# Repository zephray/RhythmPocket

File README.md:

# RhythmPocket
Pocket audio player inside GameBoy case

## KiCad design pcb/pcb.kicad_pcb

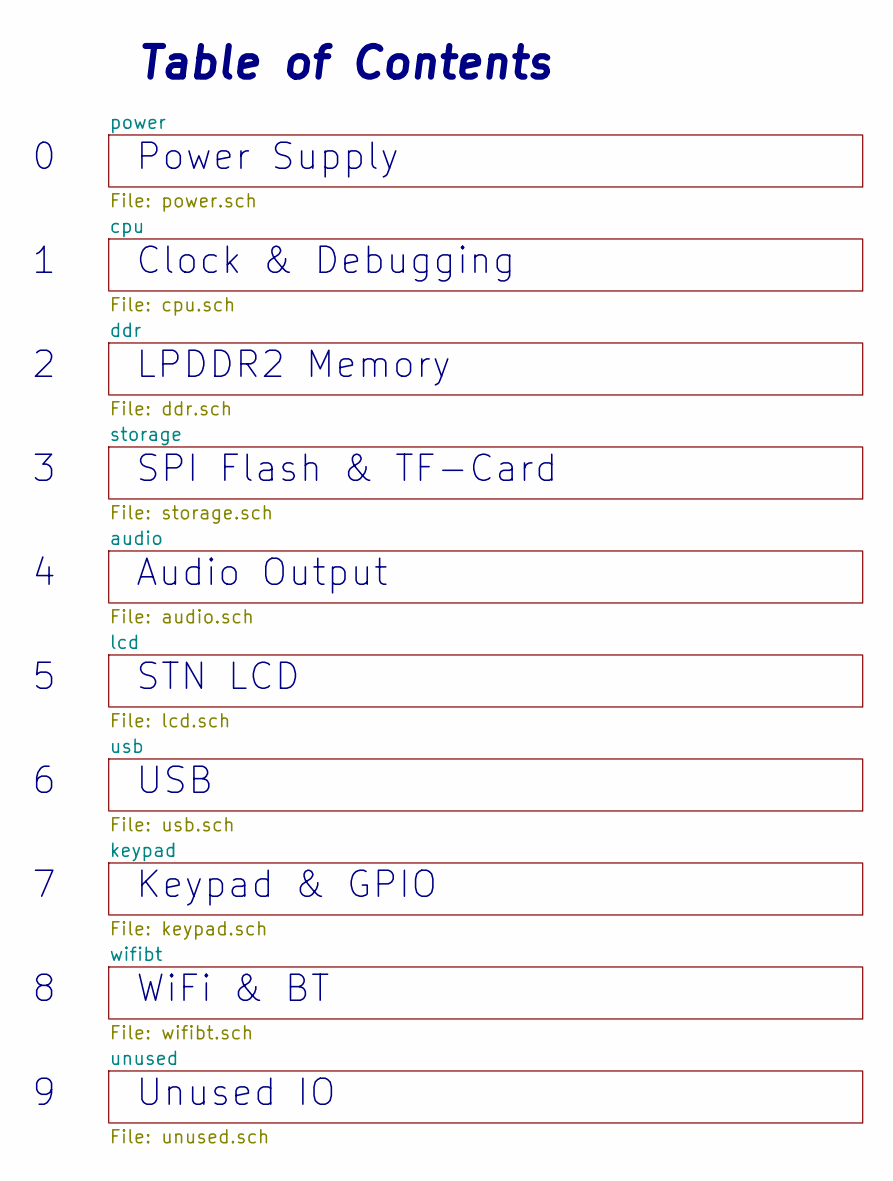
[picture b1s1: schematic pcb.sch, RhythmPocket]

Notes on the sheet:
Clock & Debugging
LPDDR2 Memory
STN LCD
SPI Flash & TF-Card
Table of Contents
Power Supply
Audio Output
Keypad & GPIO
Unused IO
USB
WiFi & BT

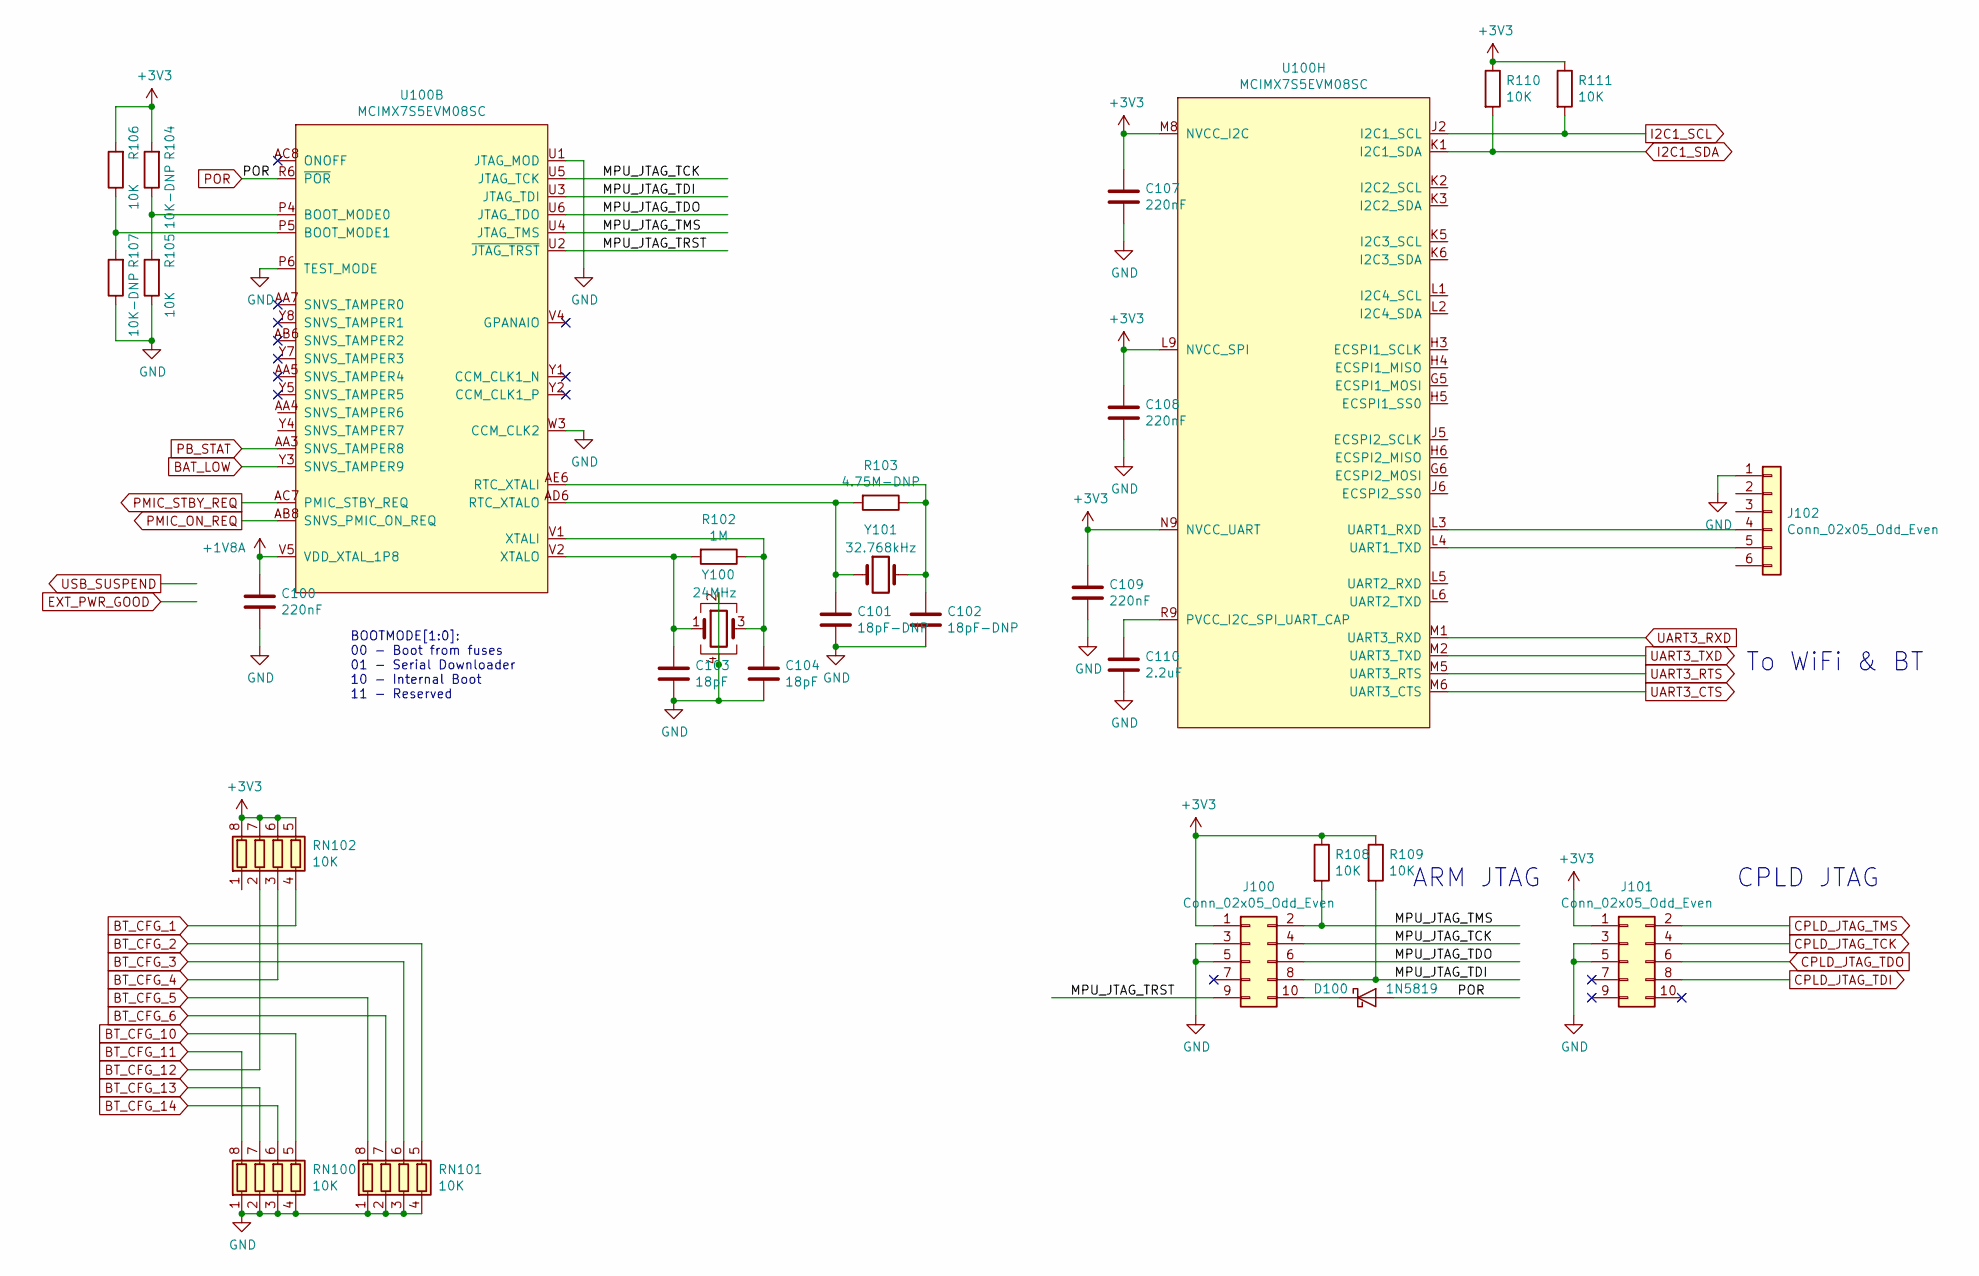
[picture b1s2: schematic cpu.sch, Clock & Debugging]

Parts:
C100, C107, C108, C109: 220nF; C_0402_1005Metric
C101, C102: 18pF-DNP; C_0402_1005Metric
C103, C104: 18pF; C_0402_1005Metric
C110: 2.2uF; C_0402_1005Metric
D100: 1N5819; D_SOD-123
J100, J101, J102: Conn_02x05_Odd_Even; PinHeader_2x05_P1.27mm_Vertical_SMD
R102: 1M; R_0603_1608Metric
R103: 4.75M-DNP; R_0603_1608Metric
R104, R107: 10K-DNP; R_0603_1608Metric
R105, R106, R108, R109, R110, R111: 10K; R_0603_1608Metric
RN100, RN101, RN102: 10K; R_Array_Convex_4x0402
U100: MCIMX7S5EVM08SC; BGA-541_25x25_19.0x19.0mm
Y100: 24MHz; Oscillator_SMD_Abracon_ASE-4Pin_3.2x2.5mm
Y101: 32.768kHz; Crystal_SMD_TXC_9HT11-2Pin_2.0x1.2mm_HandSoldering

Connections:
+1V8A: C100.1, U100.V5 (VDD_XTAL_1P8)
+3V3: C107.1, C108.1, C109.1, J100.1, J101.1, R104.2, R106.2, R108.1, R109.1, R110.1, R111.1, RN102.5 (R4.2), RN102.6 (R3.2), RN102.7 (R2.2), RN102.8 (R1.2), U100.L9 (NVCC_SPI), U100.M8 (NVCC_I2C), U100.N9 (NVCC_UART); also elsewhere on the board
/cpu/MPU_JTAG_TCK: J100.4, U100.U5 (JTAG_TCK)
/cpu/MPU_JTAG_TDI: J100.8, R109.2, U100.U3 (JTAG_TDI)
/cpu/MPU_JTAG_TDO: J100.6, U100.U6 (JTAG_TDO)
/cpu/MPU_JTAG_TMS: J100.2, R108.2, U100.U4 (JTAG_TMS)
/cpu/MPU_JTAG_TRST: J100.9, U100.U2 (~JTAG_TRST)
BAT_LOW: U100.Y3 (SNVS_TAMPER9); also elsewhere on the board
BT_CFG_1: RN102.4 (R4.1); also elsewhere on the board
BT_CFG_2: RN101.5 (R4.2); also elsewhere on the board
BT_CFG_3: RN101.6 (R3.2); also elsewhere on the board
BT_CFG_4: RN102.3 (R3.1); also elsewhere on the board
BT_CFG_5: RN101.8 (R1.2); also elsewhere on the board
BT_CFG_6: RN101.7 (R2.2); also elsewhere on the board
BT_CFG_10: RN100.5 (R4.2); also elsewhere on the board
BT_CFG_11: RN100.8 (R1.2); also elsewhere on the board
BT_CFG_12: RN102.2 (R2.1); also elsewhere on the board
BT_CFG_13: RN100.7 (R2.2); also elsewhere on the board
BT_CFG_14: RN100.6 (R3.2); also elsewhere on the board
CPLD_JTAG_TCK: J101.4; also elsewhere on the board
CPLD_JTAG_TDI: J101.8; also elsewhere on the board
CPLD_JTAG_TDO: J101.6; also elsewhere on the board
CPLD_JTAG_TMS: J101.2; also elsewhere on the board
GND: C100.2, C101.2, C102.2, C103.2, C104.2, C107.2, C108.2, C109.2, C110.2, J100.3, J100.5, J101.3, J101.5, J102.1, R105.1, R107.1, RN100.1 (R1.1), RN100.2 (R2.1), RN100.3 (R3.1), RN100.4 (R4.1), RN101.1 (R1.1), RN101.2 (R2.1), RN101.3 (R3.1), RN101.4 (R4.1), U100.P6 (TEST_MODE), U100.U1 (JTAG_MOD), U100.W3 (CCM_CLK2), Y100.2, Y100.4; also elsewhere on the board
I2C1_SCL: R111.2, U100.J2 (I2C1_SCL); also elsewhere on the board
I2C1_SDA: R110.2, U100.K1 (I2C1_SDA); also elsewhere on the board
unnamed: C101.1, R103.2, U100.AD6 (RTC_XTALO), Y101.1
unnamed: C102.1, R103.1, U100.AE6 (RTC_XTALI), Y101.2
unnamed: C103.1, R102.2, U100.V2 (XTALO), Y100.1
unnamed: C104.1, R102.1, U100.V1 (XTALI), Y100.3
unnamed: C110.1, U100.R9 (PVCC_I2C_SPI_UART_CAP)
unnamed: D100.1 (K), J100.10
unnamed: J102.4, U100.L3 (UART1_RXD)
unnamed: J102.5, U100.L4 (UART1_TXD)
unnamed: R104.1, R105.2, U100.P4 (BOOT_MODE0)
unnamed: R106.1, R107.2, U100.P5 (BOOT_MODE1)
PB_STAT: U100.AA3 (SNVS_TAMPER8); also elsewhere on the board
PMIC_ON_REQ: U100.AB8 (SNVS_PMIC_ON_REQ); also elsewhere on the board
POR: D100.2 (A), U100.R6 (~POR); also elsewhere on the board
UART3_RTS: U100.M5 (UART3_RTS); also elsewhere on the board
UART3_RXD: U100.M1 (UART3_RXD); also elsewhere on the board
UART3_TXD: U100.M2 (UART3_TXD); also elsewhere on the board

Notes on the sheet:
BOOTMODE[1:0]: 00 - Boot from fuses 01 - Serial Downloader 10 - Internal Boot 11 - Reserved
ARM JTAG
CPLD JTAG
To WiFi & BT

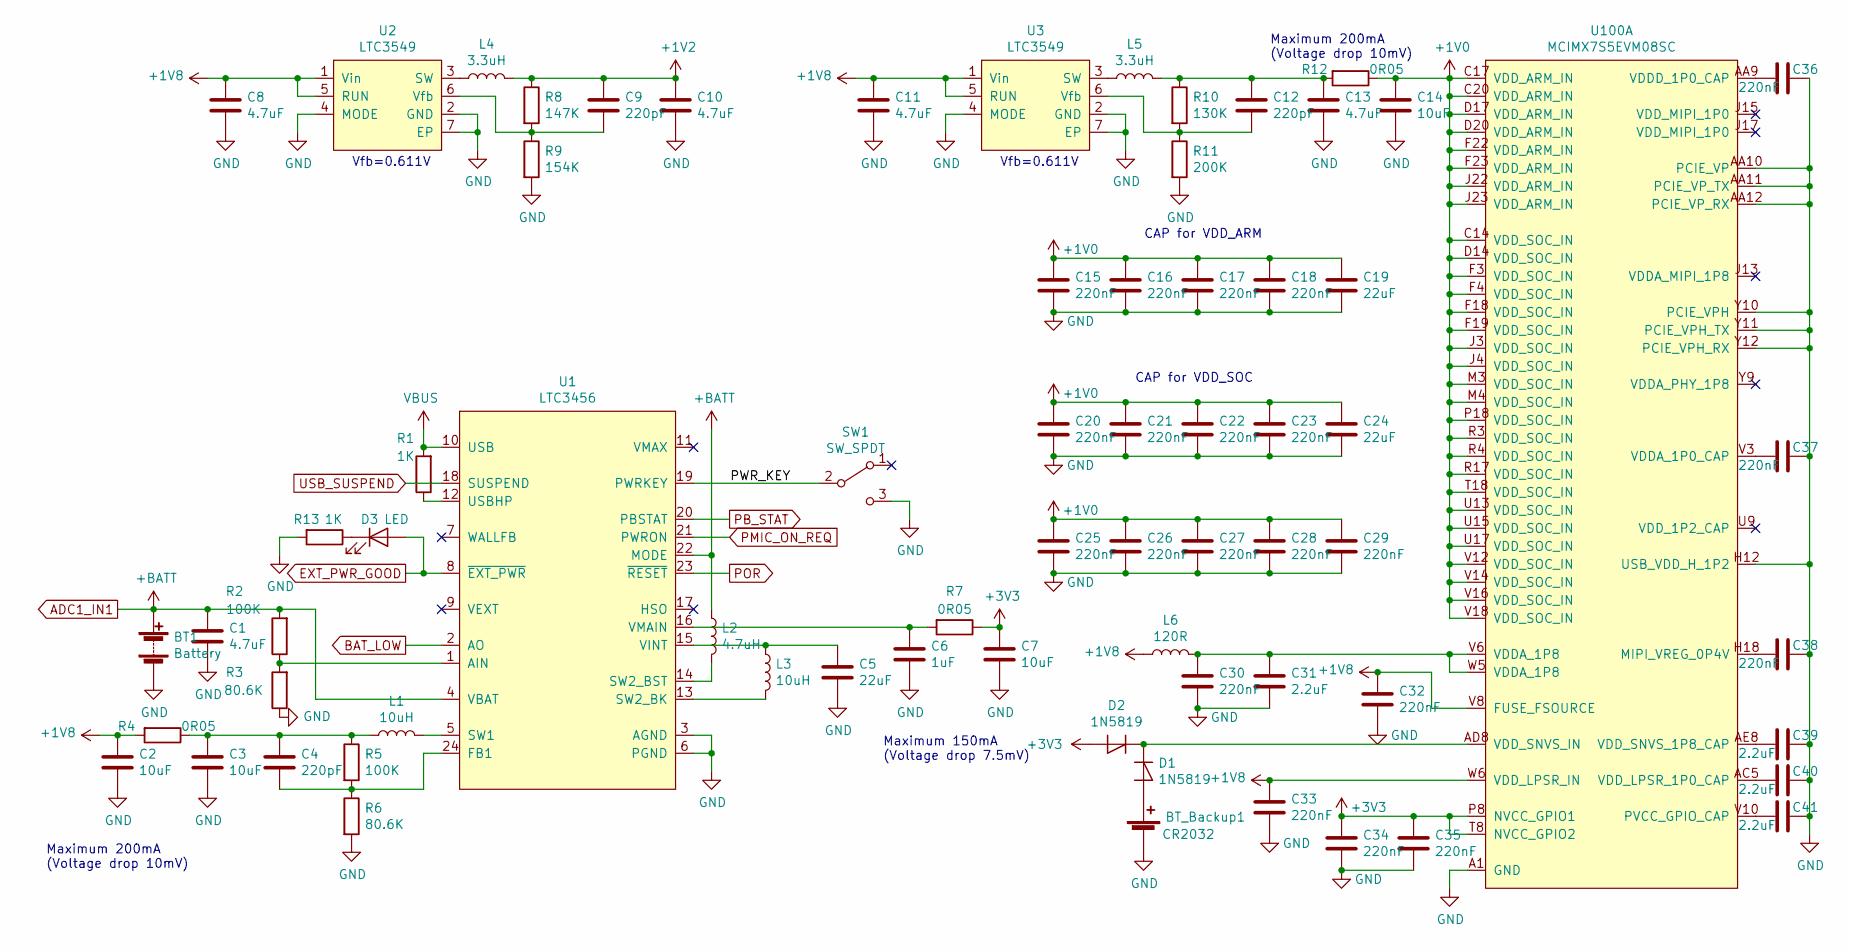
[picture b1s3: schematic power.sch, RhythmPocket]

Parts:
BT1: Battery; BatteryHolder_Keystone_2468_2xAAA
BT_Backup1: CR2032; BatteryHolder_CR1220
C1, C8, C10, C11, C13: 4.7uF; C_0603_1608Metric
C2, C3, C7, C14: 10uF; C_0603_1608Metric
C4, C9, C12: 220pF; C_0402_1005Metric
C5, C19, C24: 22uF; C_0603_1608Metric
C6: 1uF; C_0402_1005Metric
C15, C16, C17, C18, C20, C21, C22, C23, C25, C26, C27, C28, C29, C30, C32, C33, C34, C35, C36, C37, C38: 220nF; C_0402_1005Metric
C31, C39, C40, C41: 2.2uF; C_0402_1005Metric
D1, D2: 1N5819; D_SOD-123
D3: LED; LED_D5.0mm
L1, L3: 10uH; L_Vishay_IHLP-1212
L2: 4.7uH; L_Vishay_IHLP-1212
L4, L5: 3.3uH; L_Vishay_IHLP-1212
L6: 120R; L_0402_1005Metric
R1, R13: 1K; R_0603_1608Metric
R2, R5: 100K; R_0603_1608Metric
R3, R6: 80.6K; R_0603_1608Metric
R4, R7, R12: 0R05; R_1210_3225Metric
R8: 147K; R_0603_1608Metric
R9: 154K; R_0603_1608Metric
R10: 130K; R_0603_1608Metric
R11: 200K; R_0603_1608Metric
SW1: SW_SPDT; SW_SPDT_PCM12
U1: LTC3456; VQFN-24-1EP_4x4mm_P0.5mm_EP2.45x2.45mm_ThermalVias
U2, U3: LTC3549; DFN-6-1EP_3x2mm_P0.5mm_EP1.65x1.35mm
U100: MCIMX7S5EVM08SC; BGA-541_25x25_19.0x19.0mm

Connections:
+1V0: C14.1, C15.1, C16.1, C17.1, C18.1, C19.1, C20.1, C21.1, C22.1, C23.1, C24.1, C25.1, C26.1, C27.1, C28.1, C29.1, R12.1, U100.C14 (VDD_SOC_IN), U100.C17 (VDD_ARM_IN), U100.C20 (VDD_ARM_IN), U100.D14 (VDD_SOC_IN), U100.D17 (VDD_ARM_IN), U100.D20 (VDD_ARM_IN), U100.F3 (VDD_SOC_IN), U100.F4 (VDD_SOC_IN), U100.F18 (VDD_SOC_IN), U100.F19 (VDD_SOC_IN), U100.F22 (VDD_ARM_IN), U100.F23 (VDD_ARM_IN), U100.J3 (VDD_SOC_IN), U100.J4 (VDD_SOC_IN), U100.J22 (VDD_ARM_IN), U100.J23 (VDD_ARM_IN), U100.M3 (VDD_SOC_IN), U100.M4 (VDD_SOC_IN), U100.P18 (VDD_SOC_IN), U100.R3 (VDD_SOC_IN), U100.R4 (VDD_SOC_IN), U100.R17 (VDD_SOC_IN), U100.T18 (VDD_SOC_IN), U100.U13 (VDD_SOC_IN), U100.U15 (VDD_SOC_IN), U100.U17 (VDD_SOC_IN), U100.V12 (VDD_SOC_IN), U100.V14 (VDD_SOC_IN), U100.V16 (VDD_SOC_IN), U100.V18 (VDD_SOC_IN)
+1V2: C9.1, C10.1, L4.2, R8.1; also elsewhere on the board
+1V8: C2.1, C8.1, C11.1, C32.1, C33.1, L6.1, R4.2, U2.1 (Vin), U2.5 (RUN), U3.1 (Vin), U3.5 (RUN), U100.V8 (FUSE_FSOURCE), U100.W6 (VDD_LPSR_IN); also elsewhere on the board
+3V3: C7.1, C34.1, C35.1, D2.2 (A), R7.1, U100.P8 (NVCC_GPIO1), U100.T8 (NVCC_GPIO2); also elsewhere on the board
/power/PWR_KEY: SW1.2 (B), U1.19 (PWRKEY)
ADC1_IN1: BT1.1 (+), C1.1, L2.1, R2.2, U1.4 (VBAT), U1.22 (MODE); also elsewhere on the board
BAT_LOW: U1.2 (AO); also elsewhere on the board
EXT_PWR_GOOD: D3.2 (A), U1.8 (~EXT_PWR)
GND: BT1.2 (-), BT_Backup1.2 (-), C1.2, C2.2, C3.2, C5.2, C6.2, C7.2, C8.2, C10.2, C11.2, C13.2, C14.2, C15.2, C16.2, C17.2, C18.2, C19.2, C20.2, C21.2, C22.2, C23.2, C24.2, C25.2, C26.2, C27.2, C28.2, C29.2, C30.2, C31.2, C32.2, C33.2, C34.2, C35.2, C36.1, C37.1, C38.1, C39.1, C40.1, C41.1, R3.1, R6.2, R9.2, R11.2, R13.2, SW1.3 (C), U1.3 (AGND), U1.6 (PGND), U2.2 (GND), U2.4 (MODE), U2.7 (EP), U3.2 (GND), U3.4 (MODE), U3.7 (EP), U100.A1 (GND), U100.A3 (GND), U100.A6 (GND), U100.A9 (GND), U100.A13 (GND), U100.A17 (GND), U100.A21 (GND), U100.A25 (GND), U100.AA1 (GND), U100.AA2 (GND), U100.AA6 (GND), U100.AA8 (GND), U100.AA10 (PCIE_VP), U100.AA11 (PCIE_VP_TX), U100.AA12 (PCIE_VP_RX), U100.AA15 (GND), U100.AA23 (GND), U100.AB4 (GND), U100.AB5 (GND), U100.AB7 (GND), U100.AB9 (GND), U100.AB12 (GND), U100.AC6 (GND), U100.AC9 (GND), U100.AC12 (GND), U100.AC15 (GND), U100.AC17 (GND), U100.AC19 (GND), U100.AC21 (GND), U100.AC23 (GND), U100.AD2 (GND), U100.AD5 (GND), U100.AD7 (GND), U100.AD9 (GND), U100.AD12 (GND), U100.AE1 (GND), U100.AE5 (GND), U100.AE7 (GND), U100.AE9 (GND), U100.AE12 (GND), U100.AE24 (GND), U100.AE25 (GND), U100.B3 (GND), U100.B6 (GND), U100.B9 (GND), U100.B13 (GND), U100.B17 (GND), U100.B21 (GND), U100.C9 (GND), U100.C13 (GND), U100.C15 (GND), U100.C16 (GND), U100.C18 (GND), U100.C19 (GND), U100.D1 (GND), U100.D2 (GND), U100.D4 (GND), U100.D7 (GND), U100.D10 (GND), U100.D22 (GND), U100.F7 (GND), U100.F8 (GND), U100.F11 (GND), U100.F13 (GND), U100.G4 (GND), U100.G7 (GND), U100.G9 (GND), U100.G11 (GND), U100.G13 (GND), U100.G15 (GND), U100.G17 (GND), U100.G19 (GND), U100.G22 (GND), U100.H1 (GND), U100.H2 (GND), U100.H12 (USB_VDD_H_1P2), U100.J7 (GND), U100.J19 (GND), U100.K4 (GND), U100.K10 (GND), U100.K12 (GND), U100.K14 (GND), U100.K16 (GND), U100.K22 (GND), U100.L7 (GND), U100.L11 (GND), U100.L13 (GND), U100.L15 (GND), U100.L19 (GND), U100.M10 (GND), U100.M12 (GND), U100.M14 (GND), U100.M16 (GND), U100.M24 (GND), U100.M25 (GND), U100.N4 (GND), U100.N7 (GND), U100.N11 (GND), U100.N13 (GND), U100.N15 (GND), U100.N19 (GND), U100.P10 (GND), U100.P12 (GND), U100.P14 (GND), U100.P16 (GND), U100.R7 (GND), U100.R11 (GND), U100.R13 (GND), U100.R15 (GND), U100.R19 (GND), U100.R20 (GND), U100.R21 (GND), U100.R23 (GND), U100.T4 (GND), U100.T10 (GND), U100.T12 (GND), U100.T14 (GND), U100.T16 (GND), U100.T20 (GND), U100.U7 (GND), U100.U11 (GND), U100.U19 (GND), U100.U20 (GND), U100.U23 (GND), U100.V20 (GND), U100.W1 (GND), U100.W2 (GND), U100.W4 (GND), U100.W7 (GND), U100.W9 (GND), U100.W11 (GND), U100.W13 (GND), U100.W15 (GND), U100.W17 (GND), U100.W19 (GND), U100.W20 (GND), U100.W23 (GND), U100.Y6 (GND), U100.Y10 (PCIE_VPH), U100.Y11 (PCIE_VPH_TX), U100.Y12 (PCIE_VPH_RX), U100.Y13 (GND), U100.Y14 (GND), U100.Y15 (GND), U100.Y16 (GND), U100.Y17 (GND), U100.Y18 (GND), U100.Y19 (GND); also elsewhere on the board
unnamed: BT_Backup1.1 (+), D1.2 (A)
unnamed: C3.1, C4.1, L1.1, R4.1, R5.1
unnamed: C4.2, R5.2, R6.1, U1.24 (FB1)
unnamed: C5.1, L3.1, U1.15 (VINT)
unnamed: C6.1, R7.2, U1.16 (VMAIN)
unnamed: C9.2, R8.2, R9.1, U2.6 (Vfb)
unnamed: C12.1, C13.1, L5.2, R10.1, R12.2
unnamed: C12.2, R10.2, R11.1, U3.6 (Vfb)
unnamed: C30.1, C31.1, L6.2, U100.V6 (VDDA_1P8), U100.W5 (VDDA_1P8)
unnamed: C36.2, U100.AA9 (VDDD_1P0_CAP)
unnamed: C37.2, U100.V3 (VDDA_1P0_CAP)
unnamed: C38.2, U100.H18 (MIPI_VREG_0P4V)
unnamed: C39.2, U100.AE8 (VDD_SNVS_1P8_CAP)
unnamed: C40.2, U100.AC5 (VDD_LPSR_1P0_CAP)
unnamed: C41.2, U100.V10 (PVCC_GPIO_CAP)
unnamed: D1.1 (K), D2.1 (K), U100.AD8 (VDD_SNVS_IN)
unnamed: D3.1 (K), R13.1
unnamed: L1.2, U1.5 (SW1)
unnamed: L2.2, U1.14 (SW2_BST)
unnamed: L3.2, U1.13 (SW2_BK)
unnamed: L4.1, U2.3 (SW)
unnamed: L5.1, U3.3 (SW)
unnamed: R1.1, U1.12 (USBHP)
unnamed: R2.1, R3.2, U1.1 (AIN)
PB_STAT: U1.20 (PBSTAT); also elsewhere on the board
PMIC_ON_REQ: U1.21 (PWRON); also elsewhere on the board
POR: U1.23 (~RESET); also elsewhere on the board
VBUS: R1.2, U1.10 (USB); also elsewhere on the board

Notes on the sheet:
Maximum 200mA (Voltage drop 10mV)
Vfb=0.611V
Maximum 150mA (Voltage drop 7.5mV)
CAP for VDD_ARM
CAP for VDD_SOC

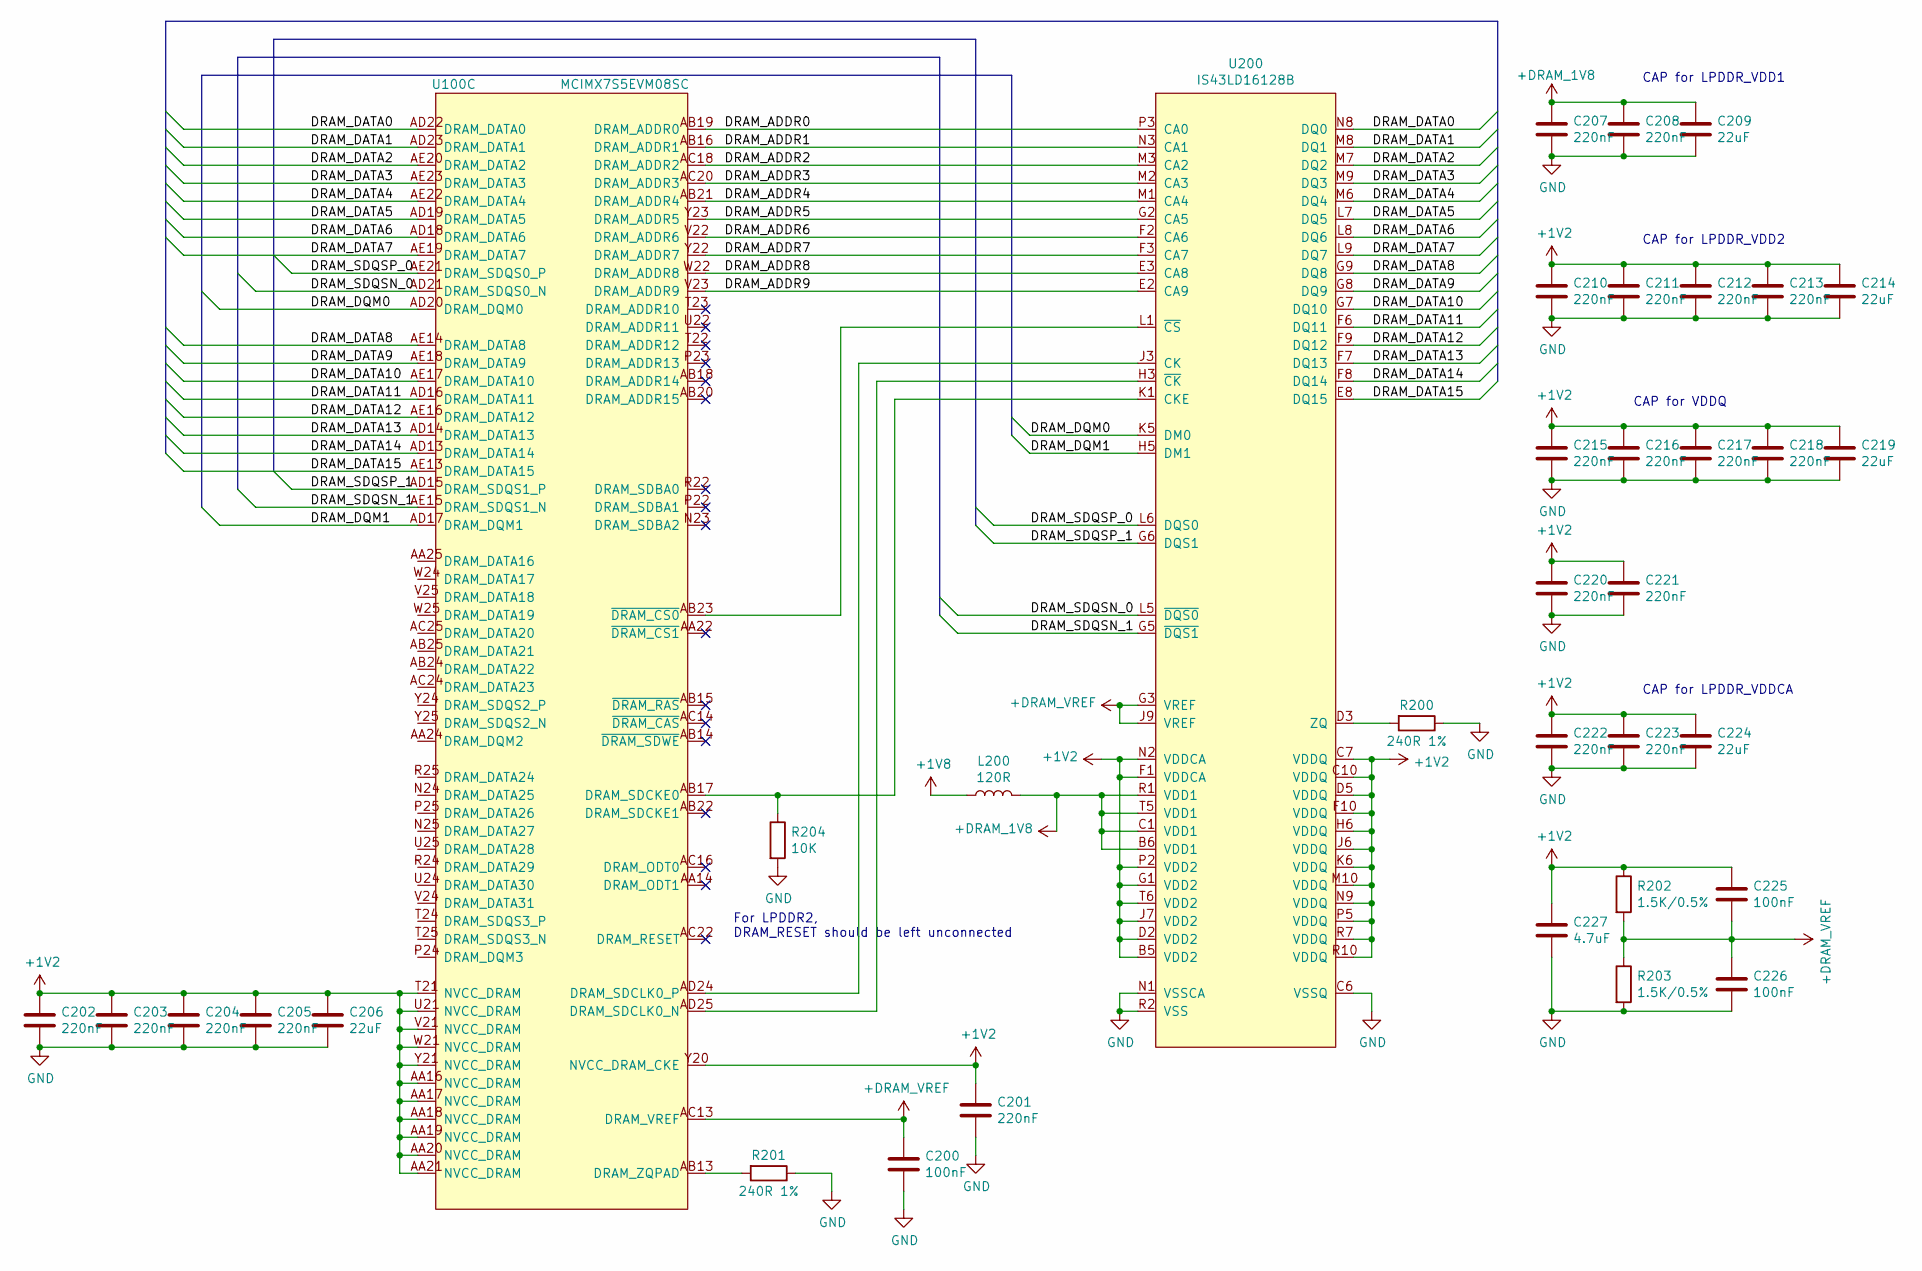
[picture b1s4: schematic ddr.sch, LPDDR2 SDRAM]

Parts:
C200, C225, C226: 100nF; C_0402_1005Metric
C201, C202, C203, C204, C205, C207, C208, C210, C211, C212, C213, C215, C216, C217, C218, C220, C221, C222, C223: 220nF; C_0402_1005Metric
C206, C209, C214, C219, C224: 22uF; C_0603_1608Metric
C227: 4.7uF; C_0603_1608Metric
L200: 120R; L_0603_1608Metric
R200, R201: 240R 1%; R_0402_1005Metric
R202, R203: 1.5K/0.5%; R_0402_1005Metric
R204: 10K; R_0402_1005Metric
U100: MCIMX7S5EVM08SC; BGA-541_25x25_19.0x19.0mm
U200: IS43LD16128B; BGA-134_10x17_10.0x11.5mm

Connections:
+1V2: C201.1, C202.1, C203.1, C204.1, C205.1, C206.1, C210.1, C211.1, C212.1, C213.1, C214.1, C215.1, C216.1, C217.1, C218.1, C219.1, C220.1, C221.1, C222.1, C223.1, C224.1, C225.1, C227.1, R202.1, U100.AA16 (NVCC_DRAM), U100.AA17 (NVCC_DRAM), U100.AA18 (NVCC_DRAM), U100.AA19 (NVCC_DRAM), U100.AA20 (NVCC_DRAM), U100.AA21 (NVCC_DRAM), U100.T21 (NVCC_DRAM), U100.U21 (NVCC_DRAM), U100.V21 (NVCC_DRAM), U100.W21 (NVCC_DRAM), U100.Y20 (NVCC_DRAM_CKE), U100.Y21 (NVCC_DRAM), U200.B5 (VDD2), U200.C7 (VDDQ), U200.C10 (VDDQ), U200.D2 (VDD2), U200.D5 (VDDQ), U200.F1 (VDDCA), U200.F10 (VDDQ), U200.G1 (VDD2), U200.H6 (VDDQ), U200.J6 (VDDQ), U200.J7 (VDD2), U200.K6 (VDDQ), U200.M10 (VDDQ), U200.N2 (VDDCA), U200.N9 (VDDQ), U200.P2 (VDD2), U200.P5 (VDDQ), U200.R7 (VDDQ), U200.R10 (VDDQ), U200.T6 (VDD2); also elsewhere on the board
+1V8: L200.1; also elsewhere on the board
+DRAM_1V8: C207.1, C208.1, C209.1, L200.2, U200.B6 (VDD1), U200.C1 (VDD1), U200.R1 (VDD1), U200.T5 (VDD1)
+DRAM_VREF: C200.1, C225.2, C226.1, R202.2, R203.1, U100.AC13 (DRAM_VREF), U200.G3 (VREF), U200.J9 (VREF)
/ddr/DRAM_ADDR0: U100.AB19 (DRAM_ADDR0), U200.P3 (CA0)
/ddr/DRAM_ADDR1: U100.AB16 (DRAM_ADDR1), U200.N3 (CA1)
/ddr/DRAM_ADDR2: U100.AC18 (DRAM_ADDR2), U200.M3 (CA2)
/ddr/DRAM_ADDR3: U100.AC20 (DRAM_ADDR3), U200.M2 (CA3)
/ddr/DRAM_ADDR4: U100.AB21 (DRAM_ADDR4), U200.M1 (CA4)
/ddr/DRAM_ADDR5: U100.Y23 (DRAM_ADDR5), U200.G2 (CA5)
/ddr/DRAM_ADDR6: U100.V22 (DRAM_ADDR6), U200.F2 (CA6)
/ddr/DRAM_ADDR7: U100.Y22 (DRAM_ADDR7), U200.F3 (CA7)
/ddr/DRAM_ADDR8: U100.W22 (DRAM_ADDR8), U200.E3 (CA8)
/ddr/DRAM_ADDR9: U100.V23 (DRAM_ADDR9), U200.E2 (CA9)
/ddr/DRAM_DATA0: U100.AD22 (DRAM_DATA0), U200.N8 (DQ0)
/ddr/DRAM_DATA1: U100.AD23 (DRAM_DATA1), U200.M8 (DQ1)
/ddr/DRAM_DATA2: U100.AE20 (DRAM_DATA2), U200.M7 (DQ2)
/ddr/DRAM_DATA3: U100.AE23 (DRAM_DATA3), U200.M9 (DQ3)
/ddr/DRAM_DATA4: U100.AE22 (DRAM_DATA4), U200.M6 (DQ4)
/ddr/DRAM_DATA5: U100.AD19 (DRAM_DATA5), U200.L7 (DQ5)
/ddr/DRAM_DATA6: U100.AD18 (DRAM_DATA6), U200.L8 (DQ6)
/ddr/DRAM_DATA7: U100.AE19 (DRAM_DATA7), U200.L9 (DQ7)
/ddr/DRAM_DATA8: U100.AE14 (DRAM_DATA8), U200.G9 (DQ8)
/ddr/DRAM_DATA9: U100.AE18 (DRAM_DATA9), U200.G8 (DQ9)
/ddr/DRAM_DATA10: U100.AE17 (DRAM_DATA10), U200.G7 (DQ10)
/ddr/DRAM_DATA11: U100.AD16 (DRAM_DATA11), U200.F6 (DQ11)
/ddr/DRAM_DATA12: U100.AE16 (DRAM_DATA12), U200.F9 (DQ12)
/ddr/DRAM_DATA13: U100.AD14 (DRAM_DATA13), U200.F7 (DQ13)
/ddr/DRAM_DATA14: U100.AD13 (DRAM_DATA14), U200.F8 (DQ14)
/ddr/DRAM_DATA15: U100.AE13 (DRAM_DATA15), U200.E8 (DQ15)
/ddr/DRAM_DQM0: U100.AD20 (DRAM_DQM0), U200.K5 (DM0)
/ddr/DRAM_DQM1: U100.AD17 (DRAM_DQM1), U200.H5 (DM1)
/ddr/DRAM_SDQSN_0: U100.AD21 (DRAM_SDQS0_N), U200.L5 (~DQS0)
/ddr/DRAM_SDQSN_1: U100.AE15 (DRAM_SDQS1_N), U200.G5 (~DQS1)
/ddr/DRAM_SDQSP_0: U100.AE21 (DRAM_SDQS0_P), U200.L6 (DQS0)
/ddr/DRAM_SDQSP_1: U100.AD15 (DRAM_SDQS1_P), U200.G6 (DQS1)
GND: C200.2, C201.2, C202.2, C203.2, C204.2, C205.2, C206.2, C207.2, C208.2, C209.2, C210.2, C211.2, C212.2, C213.2, C214.2, C215.2, C216.2, C217.2, C218.2, C219.2, C220.2, C221.2, C222.2, C223.2, C224.2, C226.2, C227.2, R200.1, R201.1, R203.2, R204.2, U200.C2 (VSS), U200.C5 (VSS), U200.C6 (VSSQ), U200.C9 (VSSQ), U200.D1 (VSS), U200.D10 (VSSQ), U200.E1 (VSSCA), U200.F5 (VSSQ), U200.G10 (VSSQ), U200.H2 (VSS), U200.J1 (VSSCA), U200.J5 (VSSQ), U200.J8 (VSS), U200.L10 (VSSQ), U200.M5 (VSSQ), U200.N1 (VSSCA), U200.N10 (VSSQ), U200.P1 (VSS), U200.P10 (VSSQ), U200.R2 (VSS), U200.R5 (VSS), U200.R6 (VSSQ), U200.R9 (VSSQ); also elsewhere on the board
unnamed: R200.2, U200.D3 (ZQ)
unnamed: R201.2, U100.AB13 (DRAM_ZQPAD)
unnamed: R204.1, U100.AB17 (DRAM_SDCKE0), U200.K1 (CKE)
unnamed: U100.AB23 (~DRAM_CS0), U200.L1 (~CS)
unnamed: U100.AD24 (DRAM_SDCLK0_P), U200.J3 (CK)
unnamed: U100.AD25 (DRAM_SDCLK0_N), U200.H3 (~CK)

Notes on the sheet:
CAP for LPDDR_VDD1
CAP for LPDDR_VDD2
CAP for VDDQ
CAP for LPDDR_VDDCA
For LPDDR2, DRAM_RESET should be left unconnected

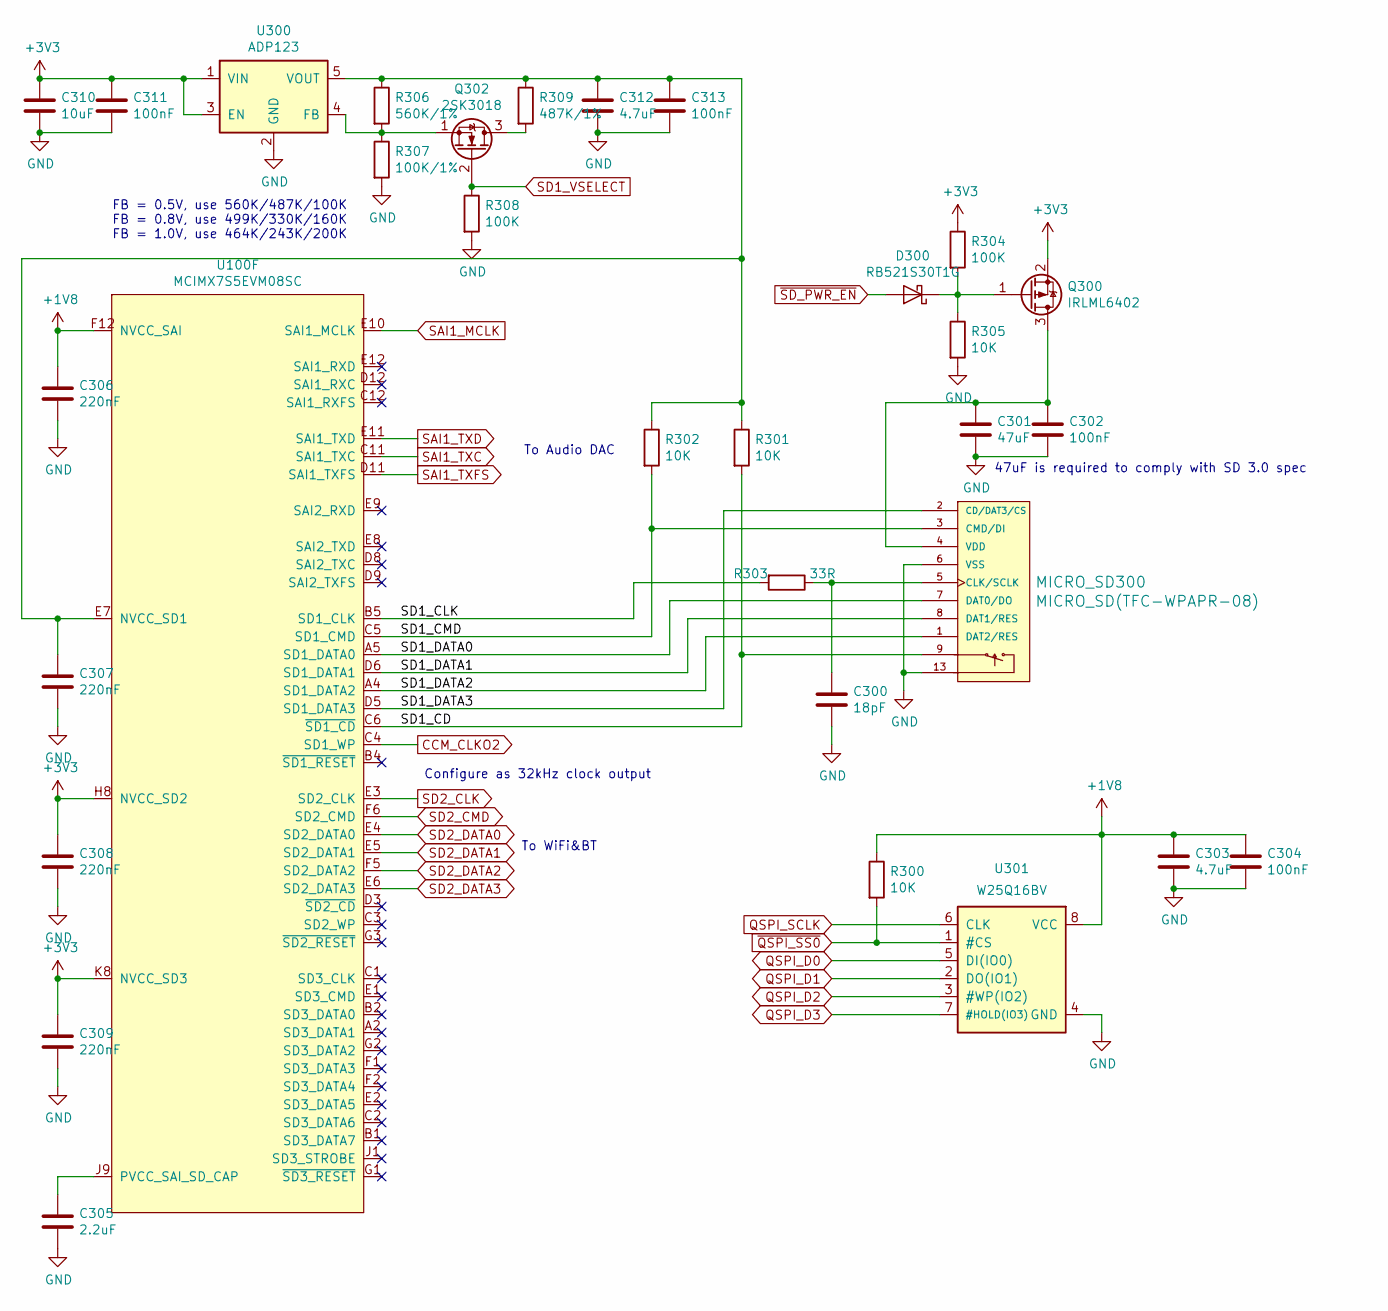
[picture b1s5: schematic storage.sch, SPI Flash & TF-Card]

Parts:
C300: 18pF; C_0402_1005Metric
C301: 47uF; C_0805_2012Metric
C302, C304, C311, C313: 100nF; C_0402_1005Metric
C303, C312: 4.7uF; C_0603_1608Metric
C305: 2.2uF; C_0402_1005Metric
C306, C307, C308, C309: 220nF; C_0402_1005Metric
C310: 10uF; C_0603_1608Metric
D300: RB521S30T1G; D_SOD-523
MICRO_SD300: MICRO_SD(TFC-WPAPR-08); TFC-WPAPR-08
Q300: IRLML6402; SOT-23
Q302: 2SK3018; SOT-23
R300, R301, R302, R305: 10K; R_0603_1608Metric
R303: 33R; R_0603_1608Metric
R304, R308: 100K; R_0603_1608Metric
R306: 560K/1%; R_0603_1608Metric
R307: 100K/1%; R_0603_1608Metric
R309: 487K/1%; R_0603_1608Metric
U100: MCIMX7S5EVM08SC; BGA-541_25x25_19.0x19.0mm
U300: ADP123; TSOT-23-5
U301: W25Q16BV; WSON-8-1EP_6x5mm_P1.27mm_EP3.4x4mm

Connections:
+1V8: C303.1, C304.1, C306.1, R300.1, U100.F12 (NVCC_SAI), U301.8 (VCC); also elsewhere on the board
+3V3: C308.1, C309.1, C310.1, C311.1, Q300.2 (S), R304.1, U100.H8 (NVCC_SD2), U100.K8 (NVCC_SD3), U300.1 (VIN), U300.3 (EN); also elsewhere on the board
/storage/SD1_CD: MICRO_SD300.9, R301.2, U100.C6 (~SD1_CD)
/storage/SD1_CLK: R303.2, U100.B5 (SD1_CLK)
/storage/SD1_CMD: MICRO_SD300.3 (CMD/DI), R302.2, U100.C5 (SD1_CMD)
/storage/SD1_DATA0: MICRO_SD300.7 (DAT0/DO), U100.A5 (SD1_DATA0)
/storage/SD1_DATA1: MICRO_SD300.8 (DAT1/RES), U100.D6 (SD1_DATA1)
/storage/SD1_DATA2: MICRO_SD300.1 (DAT2/RES), U100.A4 (SD1_DATA2)
/storage/SD1_DATA3: MICRO_SD300.2 (CD/DAT3/CS), U100.D5 (SD1_DATA3)
CCM_CLKO2: U100.C4 (SD1_WP); also elsewhere on the board
GND: C300.2, C301.2, C302.2, C303.2, C304.2, C305.2, C306.2, C307.2, C308.2, C309.2, C310.2, C311.2, C312.2, C313.2, MICRO_SD300.6 (VSS), MICRO_SD300.10, MICRO_SD300.11, MICRO_SD300.12, MICRO_SD300.13, R305.2, R307.2, R308.2, U300.2 (GND), U301.4 (GND); also elsewhere on the board
unnamed: C300.1, MICRO_SD300.5 (CLK/SCLK), R303.1
unnamed: C301.1, C302.1, MICRO_SD300.4 (VDD), Q300.3 (D)
unnamed: C305.1, U100.J9 (PVCC_SAI_SD_CAP)
unnamed: C307.1, C312.1, C313.1, R301.1, R302.1, R306.1, R309.1, U100.E7 (NVCC_SD1), U300.5 (VOUT)
unnamed: D300.1 (K), Q300.1 (G), R304.2, R305.1
unnamed: Q302.1 (S), R306.2, R307.1, U300.4 (FB)
unnamed: Q302.3 (D), R309.2
QSPI_D0: U301.5 (DI(IO0)); also elsewhere on the board
QSPI_D1: U301.2 (DO(IO1)); also elsewhere on the board
QSPI_D2: U301.3 (#WP(IO2)); also elsewhere on the board
QSPI_D3: U301.7 (#HOLD(IO3)); also elsewhere on the board
QSPI_SCLK: U301.6 (CLK); also elsewhere on the board
SAI1_MCLK: U100.E10 (SAI1_MCLK); also elsewhere on the board
SAI1_TXC: U100.C11 (SAI1_TXC); also elsewhere on the board
SAI1_TXD: U100.E11 (SAI1_TXD); also elsewhere on the board
SAI1_TXFS: U100.D11 (SAI1_TXFS); also elsewhere on the board
SD1_VSELECT: Q302.2 (G), R308.1; also elsewhere on the board
SD2_CLK: U100.E3 (SD2_CLK); also elsewhere on the board
SD2_CMD: U100.F6 (SD2_CMD); also elsewhere on the board
SD2_DATA0: U100.E4 (SD2_DATA0); also elsewhere on the board
SD2_DATA1: U100.E5 (SD2_DATA1); also elsewhere on the board
SD2_DATA2: U100.F5 (SD2_DATA2); also elsewhere on the board
SD2_DATA3: U100.E6 (SD2_DATA3); also elsewhere on the board
~QSPI_SS0: R300.2, U301.1 (#CS); also elsewhere on the board
~SD_PWR_EN: D300.2 (A); also elsewhere on the board

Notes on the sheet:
To WiFi&BT
To Audio DAC
47uF is required to comply with SD 3.0 spec
FB = 0.5V, use 560K/487K/100K FB = 0.8V, use 499K/330K/160K FB = 1.0V, use 464K/243K/200K
Configure as 32kHz clock output
